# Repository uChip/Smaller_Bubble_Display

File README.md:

# 8-digit 7-segment LED Display Module 

This repo contains Eagle CAD PCB designs for an 8-digit LED display module based on the hp bubble display. The design files include schematic, board layout and BOM files.  There is also an Eagle library file that defines the module as an Eagle component.  

The module design utilizes a shift register to reduce the number of pins required to control the display.  

The software folder contains an Arduino sketch that provides example code to drive the display.   

See the file Forum-Posting.pdf for a more detailed explanation of the module design and software.  

## Order PCBs  

You can order this PCB directly from OSH Park.  Click on the following link.  
  * 8-digit Display Module - http://oshpark.com/shared_projects/oSSTCt4N 

See the Bill of Materials (BOM) file in the repo for a parts list.  

## Status  
  * Rev2 PCB has been tested to be functional.  

## File Formats  

Hardware design files are in "CadSoft EAGLE PCB Design Software" .brd and .sch formats.  A free version of the software can be downloaded from www.cadsoftusa.com. 

The example code is in Arduino .ino format (text).  A free version of the Arduino software can be downloaded from www.arduino.cc.  

## Distribution License  

You may use this PCB design however you like but no liability is accepted.

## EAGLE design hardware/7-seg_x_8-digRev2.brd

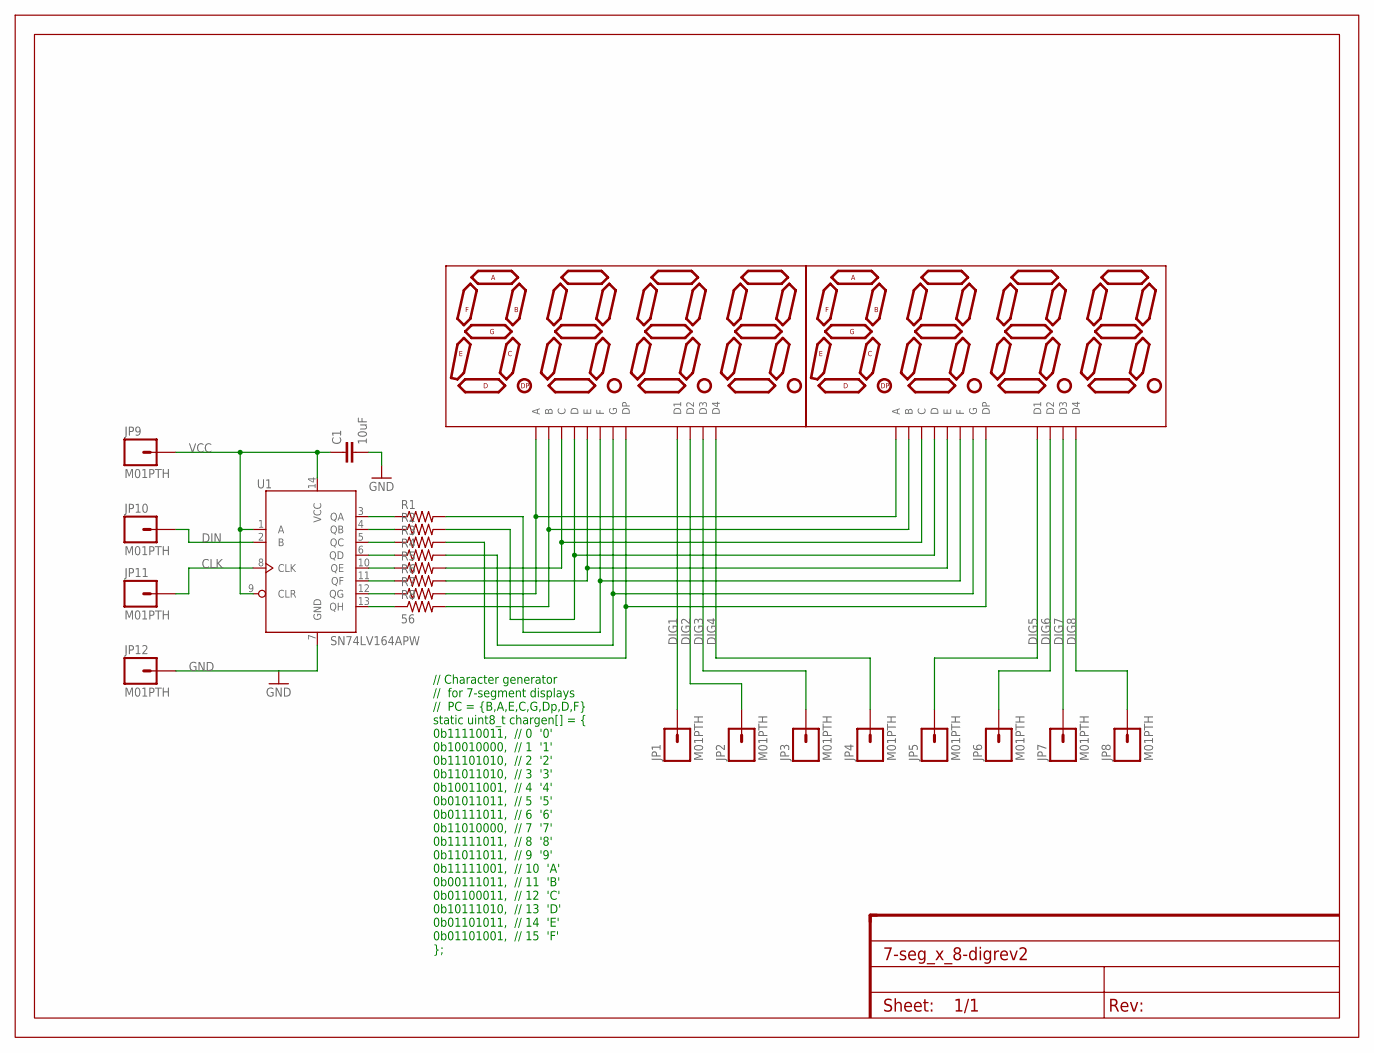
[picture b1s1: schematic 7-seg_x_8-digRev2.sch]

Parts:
C1: 10uF; 0805
FRAME1: FRAME_LTR_CU_MARK; FR-LTR-ON-PCB
JP1, JP2, JP3, JP4, JP5, JP6, JP7, JP8, JP9, JP10, JP11, JP12: M01PTH; 1X01
R1, R2, R3, R4, R5, R6, R7: RESISTOR0805-RES; 0805
R8: 56; 0805
U1: SN74LV164APW; TSSOP-14(TI)
U$1, U$2: HP_DISPLAY; DIL12

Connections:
CLK: JP11.1, U1.8 (CLK)
DIG1: JP1.1, U$1.1 (D1)
DIG2: JP2.1, U$1.10 (D2)
DIG3: JP3.1, U$1.4 (D3)
DIG4: JP4.1, U$1.6 (D4)
DIG5: JP5.1, U$2.1 (D1)
DIG6: JP6.1, U$2.10 (D2)
DIG7: JP7.1, U$2.4 (D3)
DIG8: JP8.1, U$2.6 (D4)
DIN: JP10.1, U1.2 (B)
GND: C1.2, JP12.1, U1.7 (GND)
unnamed: R1.1, U1.3 (QA)
unnamed: R2.1, U1.4 (QB)
unnamed: R3.1, U1.5 (QC)
unnamed: R4.1, U1.6 (QD)
unnamed: R5.1, U1.10 (QE)
unnamed: R6.1, U1.11 (QF)
unnamed: R7.1, U1.12 (QG)
unnamed: R8.1, U1.13 (QH)
SEGA: R7.2, U$1.12 (A), U$2.12 (A)
SEGB: R8.2, U$1.11 (B), U$2.11 (B)
SEGC: R5.2, U$1.3 (C), U$2.3 (C)
SEGD: R2.2, U$1.8 (D), U$2.8 (D)
SEGDP: R3.2, U$1.5 (DP), U$2.5 (DP)
SEGE: R6.2, U$1.2 (E), U$2.2 (E)
SEGF: R1.2, U$1.9 (F), U$2.9 (F)
SEGG: R4.2, U$1.7 (G), U$2.7 (G)
VCC: C1.1, JP9.1, U1.1 (A), U1.9 (CLR), U1.14 (VCC)

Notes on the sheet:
// Character generator // for 7-segment displays // PC = {B,A,E,C,G,Dp,D,F} static uint8_t chargen[] = { 0b11110011, // 0 '0' 0b10010000, // 1 '1' 0b11101010, // 2 '2' 0b11011010, // 3 '3' 0b10011001, // 4 '4' 0b01011011, // 5 '5' 0b01111011, // 6 '6' 0b11010000, // 7 '7' 0b11111011, // 8 '8' 0b110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

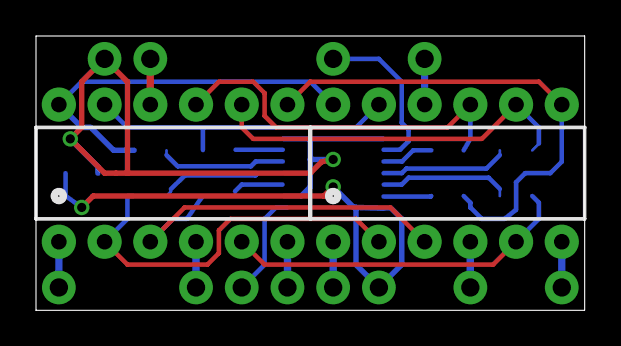
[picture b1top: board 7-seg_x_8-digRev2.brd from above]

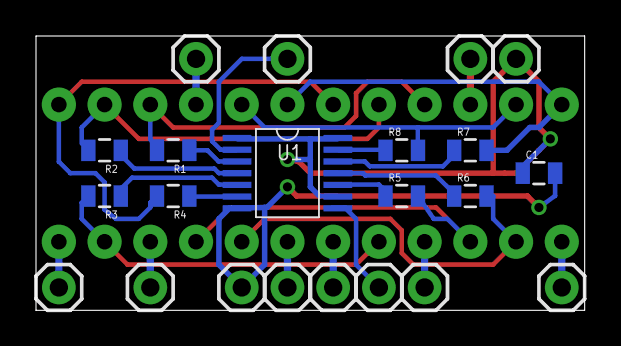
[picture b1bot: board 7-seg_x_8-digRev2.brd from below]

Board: 2 copper layers, 30.5 x 15.2 mm, 25 parts (23 on the bottom side), 28 nets.

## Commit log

2014-10-13 :boom::camel: Added .gitattributes & .gitignore files
2014-10-13 Added Eagle and Arduino files
2014-10-13 Adding README placeholder and images
2014-10-13 First cut at README. Still mostly placeholder
2014-10-13 Fiddling with README
2014-10-14 Updating library defn to point to github design files
2014-10-14 Updating to latest versions of PCB files
2014-10-28 Updated to latest board Rev & added forum posting doc

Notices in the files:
parts and their libraries:
SparkFun-Resistors: Licensing: Creative Commons ShareAlike 4.0 International - https://creativecommons.org/licenses/by-sa/4.0
